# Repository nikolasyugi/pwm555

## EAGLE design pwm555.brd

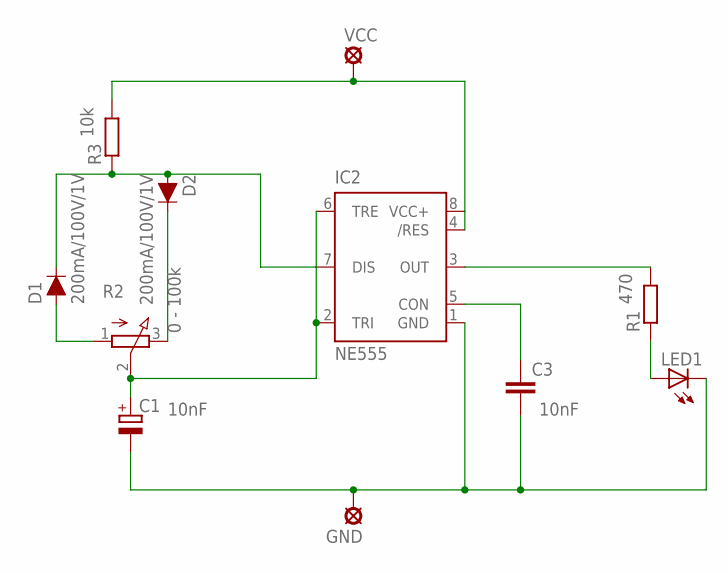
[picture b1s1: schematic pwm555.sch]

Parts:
C1: CPOL-EUE2.5-6; E2,5-6
C3: C-EU025-024X044; C025-024X044
D1, D2: 200mA/100V/1V; DIODE-1N4148
GND: LSP10
IC2: NE555; DIL-08
LED1: LED5MM
R1, R3: R-EU_0207/10; 0207/10
R2: 3RP/1610N
VCC: LSP10

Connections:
9V: IC2.4 (/RES), IC2.8 (VCC+), R3.2, VCC.MP
GND: C1.-, C3.2, GND.MP, IC2.1 (GND), LED1.K (C)
unnamed: LED1.A, R1.1
unnamed: IC2.3 (OUT), R1.2
unnamed: C3.1, IC2.5 (CON)
unnamed: C1.+, IC2.2 (TRI), IC2.6 (TRE), R2.2 (S)
unnamed: D1.A, R2.1 (A)
unnamed: D2.C, R2.3 (E)
unnamed: D1.C, D2.A, IC2.7 (DIS), R3.1

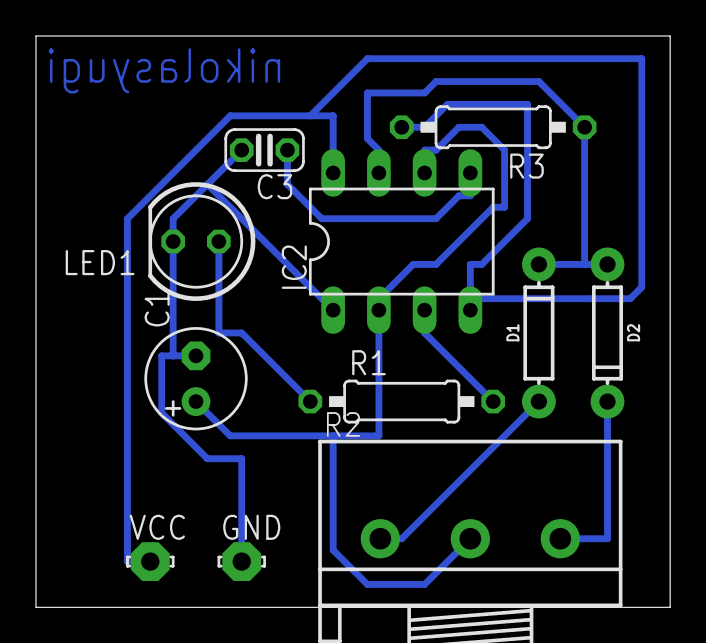
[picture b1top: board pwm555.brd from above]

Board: 2 copper layers, 35.2 x 31.7 mm, 11 parts (0 on the bottom side), 9 nets.

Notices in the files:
parts and their libraries:
SparkFun-DiscreteSemi: Licensing: Creative Commons ShareAlike 4.0 International - https://creativecommons.org/licenses/by-sa/4.0
